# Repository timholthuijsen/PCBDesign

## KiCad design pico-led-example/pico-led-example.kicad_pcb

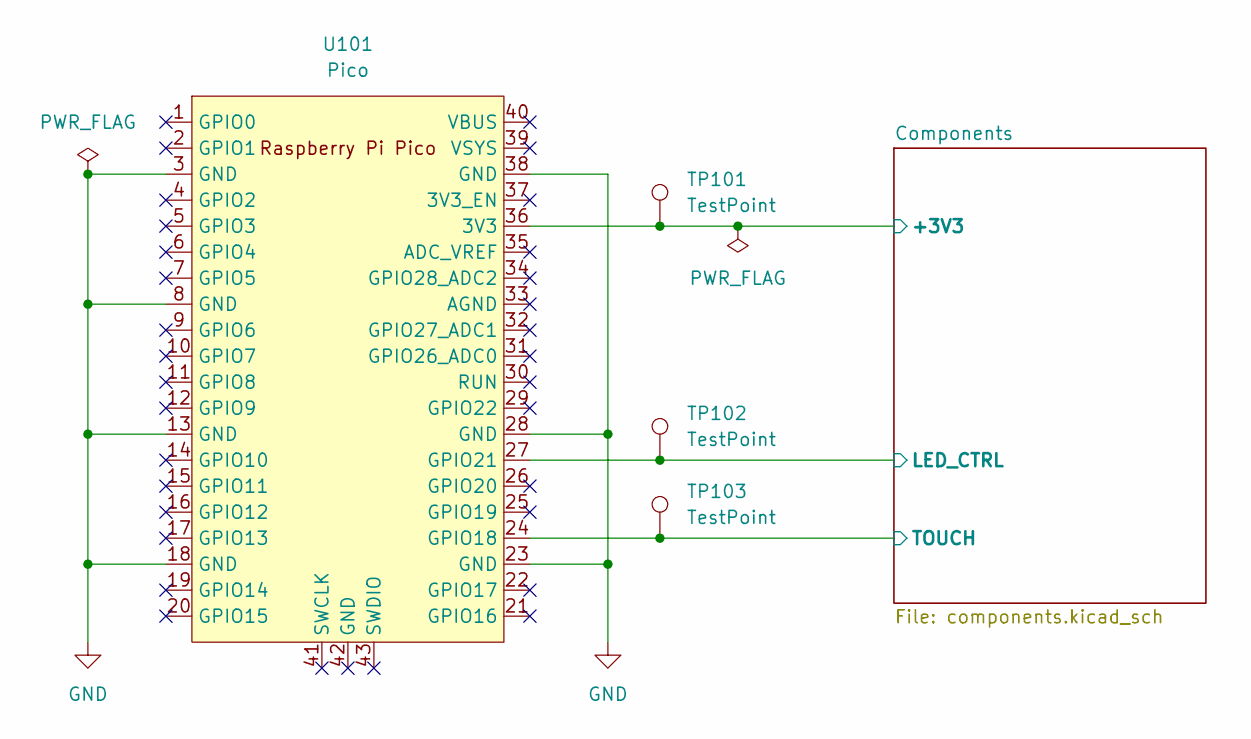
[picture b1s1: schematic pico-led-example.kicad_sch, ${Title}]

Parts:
TP101, TP102, TP103: TestPoint; TestPoint_Pad_D1.0mm
U101: Pico; RPi_Pico_SMD_TH

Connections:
/Components/+3V3: TP101.1, U101.36 (3V3); also elsewhere on the board
/Components/LED_CTRL: TP102.1, U101.27 (GPIO21); also elsewhere on the board
/Components/TOUCH: TP103.1, U101.24 (GPIO18); also elsewhere on the board
GND: U101.3 (GND), U101.8 (GND), U101.13 (GND), U101.18 (GND), U101.23 (GND), U101.28 (GND), U101.38 (GND); also elsewhere on the board

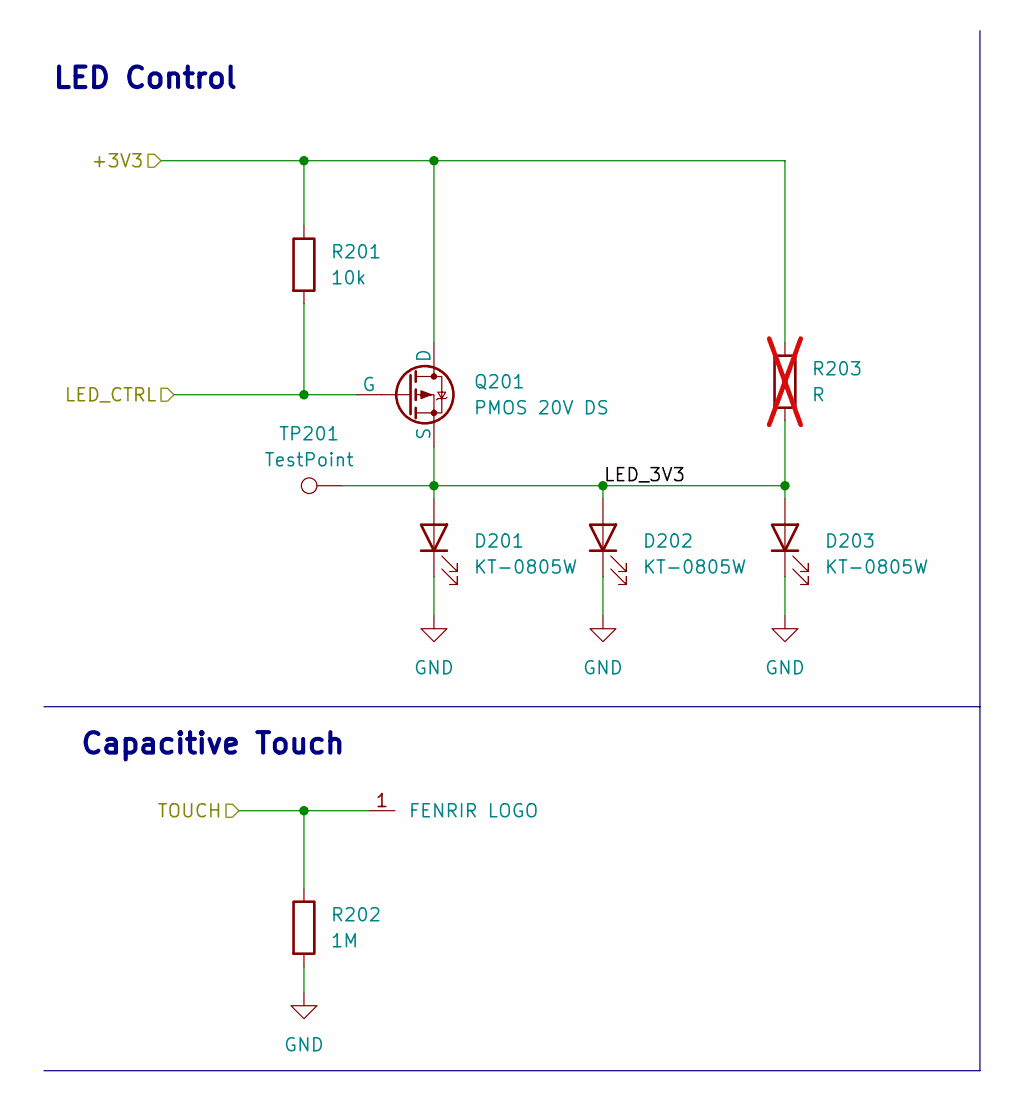
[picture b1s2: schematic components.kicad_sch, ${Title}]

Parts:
D201, D202, D203: KT-0805W; LED0805; JLCPCB Nr C34499
FENRIR201: FENRIR LOGO; FENRIR_copper_8x8mm
Q201: PMOS 20V DS; SOT-23; JLCPCB Nr C10487
R201: 10k; R_0603_1608Metric; JLCPART C25804
R202: 1M; R_0603_1608Metric; JLCPART C136593
R203: R; R_0805_2012Metric; not fitted
TP201: TestPoint; TestPoint_Pad_D1.0mm

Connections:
/Components/+3V3: Q201.3 (D), R201.1, R203.1; also elsewhere on the board
/Components/LED_3V3: D201.2 (A), D202.2 (A), D203.2 (A), Q201.2 (S), R203.2, TP201.1
/Components/LED_CTRL: Q201.1 (G), R201.2; also elsewhere on the board
/Components/TOUCH: FENRIR201.1, R202.1; also elsewhere on the board
GND: D201.1 (K), D202.1 (K), D203.1 (K), R202.2; also elsewhere on the board

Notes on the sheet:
LED Control
Capacitive Touch

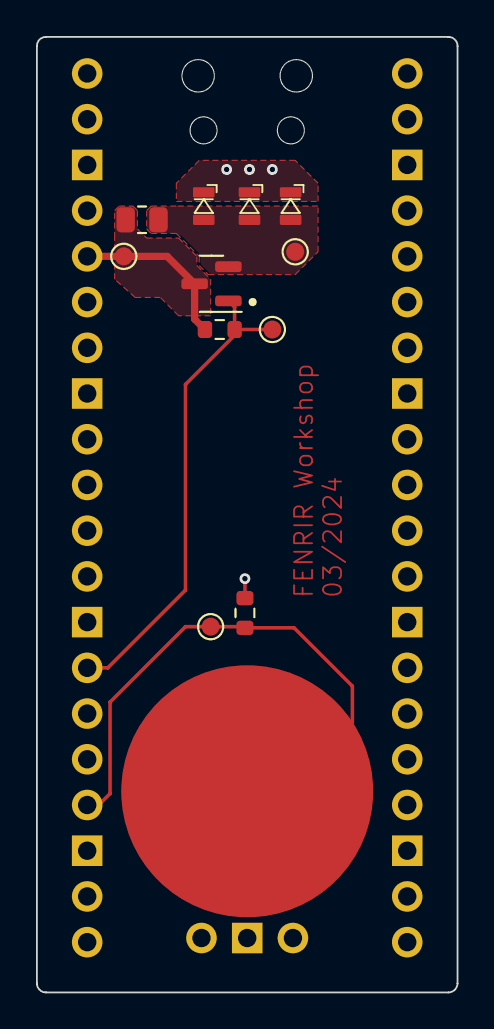
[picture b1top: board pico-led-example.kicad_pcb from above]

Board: 2 copper layers, 23.4 x 53.1 mm, 13 parts (1 on the bottom side), 5 nets.

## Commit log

2024-03-18 adding starting project
2024-03-18 adding pico submodule
